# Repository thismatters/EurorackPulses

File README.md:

# Pulses Expander (for Turing Machine)

The circuit here is a direct copy of the [Music Thing Modular Volts Expander](https://github.com/TomWhitwell/Turing-Pulse-Expander).

The KiCAD project here uses the library/footprints [found in my companion repo](https://github.com/thismatters/EurorackKiCAD).

## Width

6hp

## Inputs

The back of the module has a connection for the `pulses` output from the Turing Machine.

## Outputs

11 jacks which pulse along with the bits (and combinations thereof) on the Turing Machine.

## Vendors

There are part numbers in the [BOM](tm-pulses.csv) for many of the parts (not for basic passives though) at the following vendors:

* [Mouser](https://www.mouser.com): Needs no introduction. Get your ICs from here (or [digikey](https://www.digikey.com)).
* [Tayda Electronics](https://www.taydaelectronics.com/): Good supplier for passive components; audio jacks, and potentiometers. Their audio jacks are slightly smaller than the thonkiconn from thonk.
* [Love My Switches](https://lovemyswitches.com/): Has [really good knobs](https://lovemyswitches.com/anodized-aluminum-knob-the-lo-fi-1-4-smooth-shaft-12-5mm-od/) to go on those potentiometers!
* [OSHPark](https://oshpark.com/): Fast and (relatively) cheap PCB manufacturer. Prototype run pending.

## Changelog

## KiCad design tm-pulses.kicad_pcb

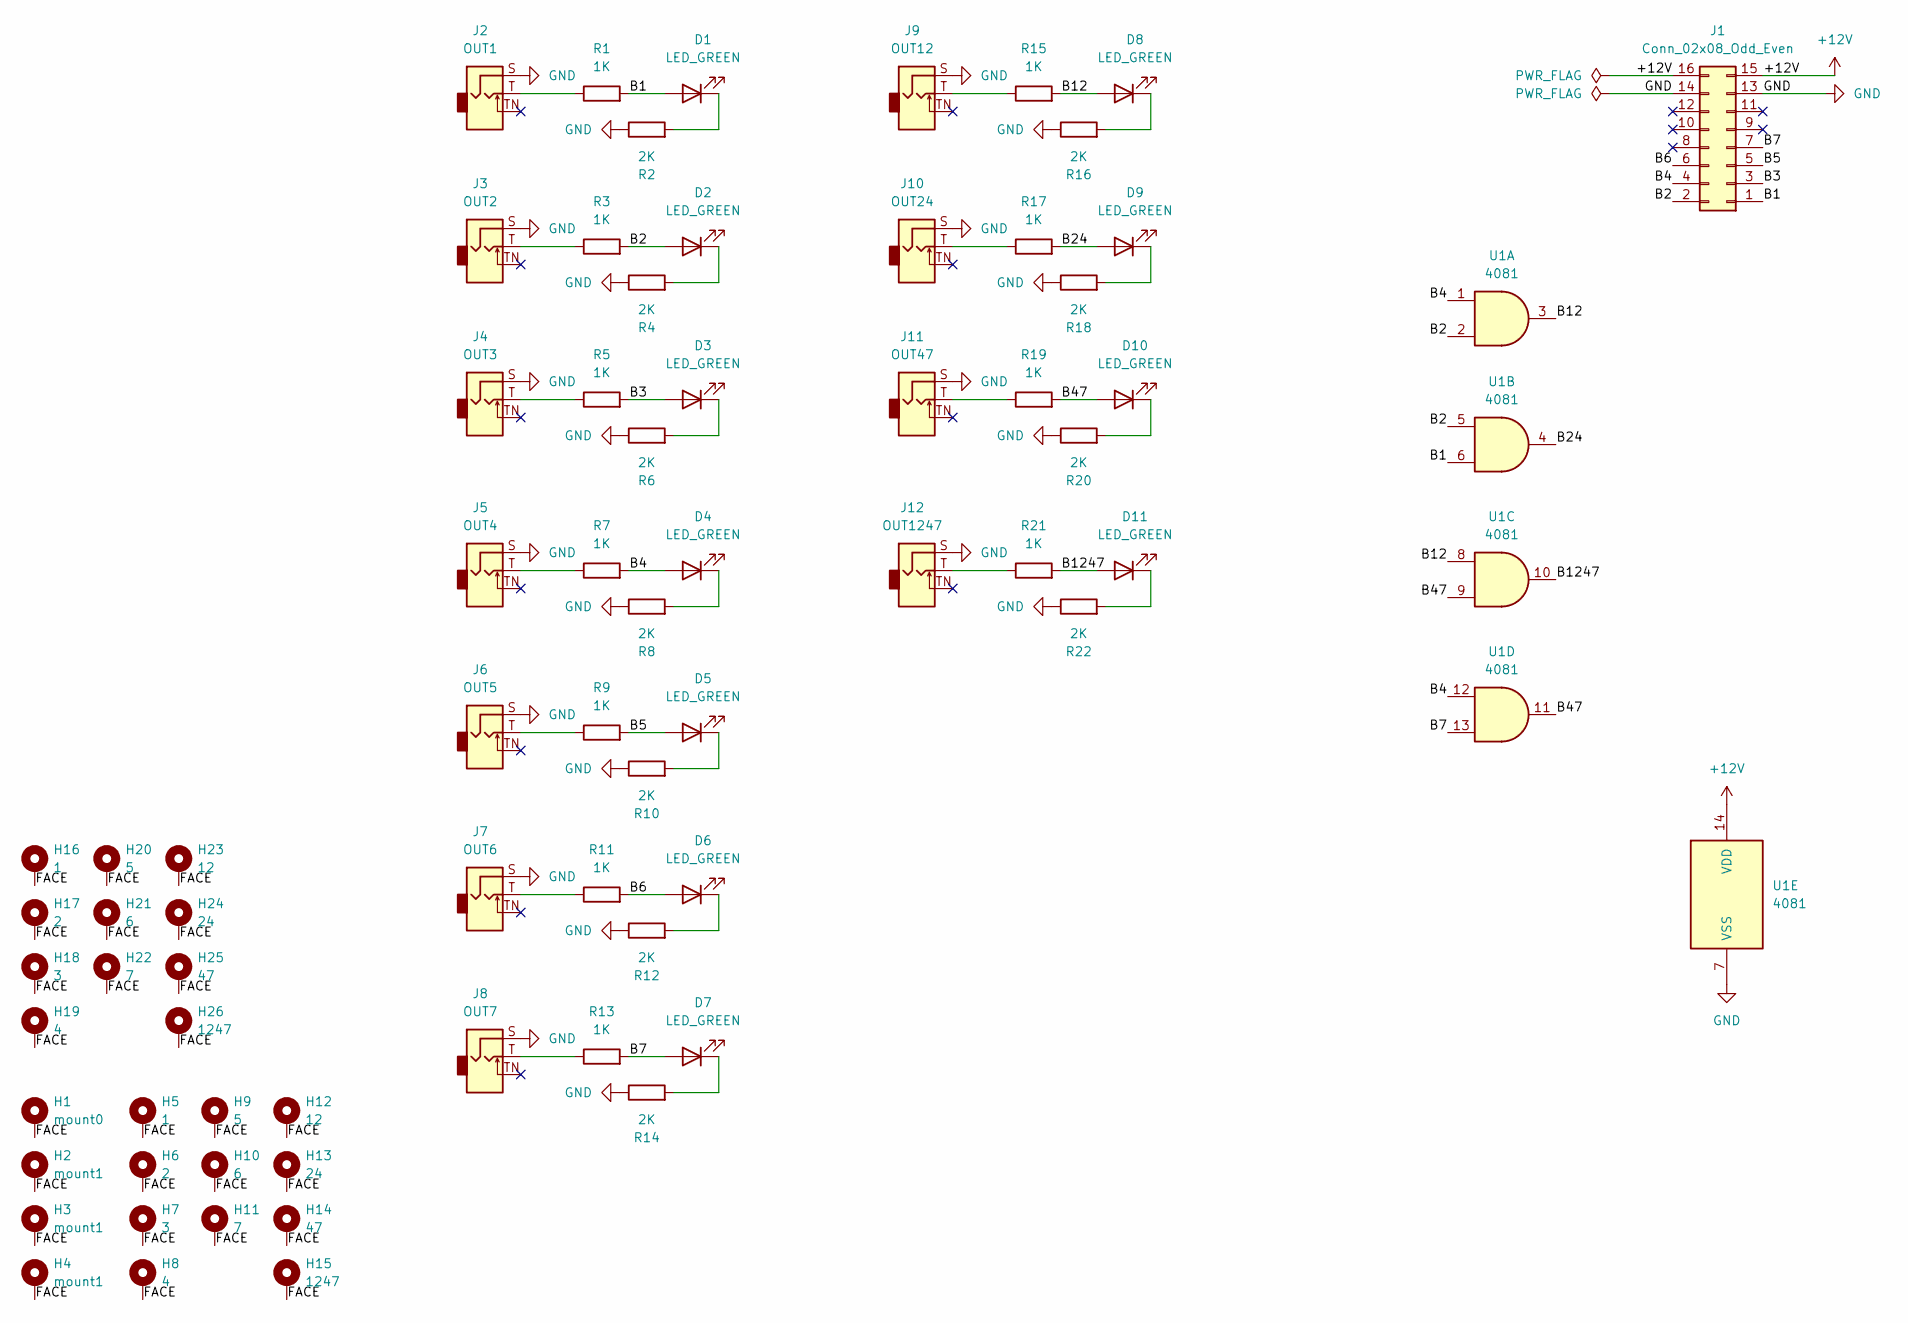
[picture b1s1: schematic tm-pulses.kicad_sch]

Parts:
D1, D2, D3, D4, D5, D6, D7, D8, D9, D10, D11: LED_GREEN; LED_D3.0mm
H1: mount0; Mech-MountingHole
H2, H3, H4: mount1; Mech-MountingHole
H5: 1; Mech-AudioJack-Hole-Output-Gate
H6: 2; Mech-AudioJack-Hole-Output-Gate
H7: 3; Mech-AudioJack-Hole-Output-Gate
H8: 4; Mech-AudioJack-Hole-Output-Gate
H9: 5; Mech-AudioJack-Hole-Output-Gate
H10: 6; Mech-AudioJack-Hole-Output-Gate
H11: 7; Mech-AudioJack-Hole-Output-Gate
H12: 12; Mech-AudioJack-Hole-Output-Gate
H13: 24; Mech-AudioJack-Hole-Output-Gate
H14: 47; Mech-AudioJack-Hole-Output-Gate
H15: 1247; Mech-AudioJack-Hole-Output-Gate
H16: 1; Mech-LED-Hole-3mm
H17: 2; Mech-LED-Hole-3mm
H18: 3; Mech-LED-Hole-3mm
H19: 4; Mech-LED-Hole-3mm
H20: 5; Mech-LED-Hole-3mm
H21: 6; Mech-LED-Hole-3mm
H22: 7; Mech-LED-Hole-3mm
H23: 12; Mech-LED-Hole-3mm
H24: 24; Mech-LED-Hole-3mm
H25: 47; Mech-LED-Hole-3mm
H26: 1247; Mech-LED-Hole-3mm
J1: Conn_02x08_Odd_Even; PinHeader_2x08_P2.54mm_Vertical; PartNum A-2956
J2: OUT1; AudioJack2_Tayda_A-2566; PartNum A-2566
J3: OUT2; AudioJack2_Tayda_A-2566; PartNum A-2566
J4: OUT3; AudioJack2_Tayda_A-2566; PartNum A-2566
J5: OUT4; AudioJack2_Tayda_A-2566; PartNum A-2566
J6: OUT5; AudioJack2_Tayda_A-2566; PartNum A-2566
J7: OUT6; AudioJack2_Tayda_A-2566; PartNum A-2566
J8: OUT7; AudioJack2_Tayda_A-2566; PartNum A-2566
J9: OUT12; AudioJack2_Tayda_A-2566; PartNum A-2566
J10: OUT24; AudioJack2_Tayda_A-2566; PartNum A-2566
J11: OUT47; AudioJack2_Tayda_A-2566; PartNum A-2566
J12: OUT1247; AudioJack2_Tayda_A-2566; PartNum A-2566
R1, R3, R5, R7, R9, R11, R13, R15, R17, R19, R21: 1K; R_0805_2012Metric
R2, R4, R6, R8, R10, R12, R14, R16, R18, R20, R22: 2K; R_0805_2012Metric
U1: 4081; TSSOP-14_4.4x5mm_P0.65mm; PartNum 595-CD4081BPWR

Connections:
+12V: J1.15, J1.16, U1.14 (VDD)
/B1: D1.2 (A), J1.1, R1.2, U1.6
/B2: D2.2 (A), J1.2, R3.2, U1.2, U1.5
/B3: D3.2 (A), J1.3, R5.2
/B4: D4.2 (A), J1.4, R7.2, U1.1, U1.12
/B5: D5.2 (A), J1.5, R9.2
/B6: D6.2 (A), J1.6, R11.2
/B7: D7.2 (A), J1.7, R13.2, U1.13
/B12: D8.2 (A), R15.2, U1.3, U1.8
/B24: D9.2 (A), R17.2, U1.4
/B47: D10.2 (A), R19.2, U1.9, U1.11
/B1247: D11.2 (A), R21.2, U1.10
/FACE: H1.1, H2.1, H3.1, H4.1, H5.1, H6.1, H7.1, H8.1, H9.1, H10.1, H11.1, H12.1, H13.1, H14.1, H15.1, H16.1, H17.1, H18.1, H19.1, H20.1, H21.1, H22.1, H23.1, H24.1, H25.1, H26.1
GND: J1.13, J1.14, J2.S, J3.S, J4.S, J5.S, J6.S, J7.S, J8.S, J9.S, J10.S, J11.S, J12.S, R2.1, R4.1, R6.1, R8.1, R10.1, R12.1, R14.1, R16.1, R18.1, R20.1, R22.1, U1.7 (VSS)
unnamed: D1.1 (K), R2.2
unnamed: D2.1 (K), R4.2
unnamed: D3.1 (K), R6.2
unnamed: D4.1 (K), R8.2
unnamed: D5.1 (K), R10.2
unnamed: D6.1 (K), R12.2
unnamed: D7.1 (K), R14.2
unnamed: D8.1 (K), R16.2
unnamed: D9.1 (K), R18.2
unnamed: D10.1 (K), R20.2
unnamed: D11.1 (K), R22.2
unnamed: J2.T, R1.1
unnamed: J3.T, R3.1
unnamed: J4.T, R5.1
unnamed: J5.T, R7.1
unnamed: J6.T, R9.1
unnamed: J7.T, R11.1
unnamed: J8.T, R13.1
unnamed: J9.T, R15.1
unnamed: J10.T, R17.1
unnamed: J11.T, R19.1
unnamed: J12.T, R21.1

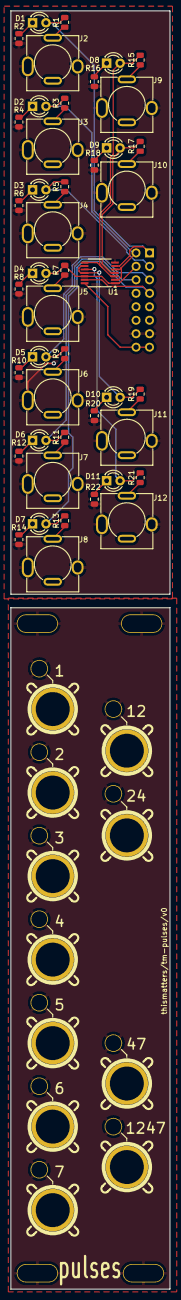
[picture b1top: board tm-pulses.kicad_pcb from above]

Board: 2 copper layers, 30.0 x 241.0 mm, 72 parts (1 on the bottom side), 36 nets.

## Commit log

2026-01-10 initial commit (v0 ready)
2026-01-10 adding schematic
2026-01-31 prefab checklist v0
